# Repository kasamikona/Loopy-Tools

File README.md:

# Kasami's Loopy Tools Collection

This is a collection of tools, scripts and info that I have created/gathered in my research and
development work on the Casio Loopy. I'm working towards splitting some parts off into dedicated repos.

**Please do not use my tools for creating controversial or offensive content.**  
I feel that the demographic of the Loopy including the modern community is not a suitable place for this.
I can't stop you from doing anything, but I will blacklist you and certainly won't provide support if you do so.
You may contact me privately if you want more of an explanation of why this notice is here.

## Related Repositories

- [Loopy-Schematics](https://github.com/kasamikona/Loopy-Schematics): Schematics for various parts and accessories.
- [loopy-homebrew-template](https://github.com/kasamikona/loopy-homebrew-template): A barebones template for homebrew.

## Repo Contents

- Documentation: Research findings and datasheets.
- Hardware: Parts for custom designed hardware.
- SerialDumper: A tool to dump cartridges using the Loopy console itself with a serial mod.
- Tools: General tools and scripts for ROM analysis and manipulation etc.
- Wanwan: Tools and scripts focused on researching and modifying the Wanwan Aijou Monogatari game.

## Licensing

Documentation and informational sections are provided on a "do what you like" basis.
Code sections may contain an appropriate LICENSE.txt to refer to,
or may have no license in which case please ask me or treat it as non-free.
In general I am assuming non-commercial use and provide no warranty.
If you have any doubts about these points, please ask!

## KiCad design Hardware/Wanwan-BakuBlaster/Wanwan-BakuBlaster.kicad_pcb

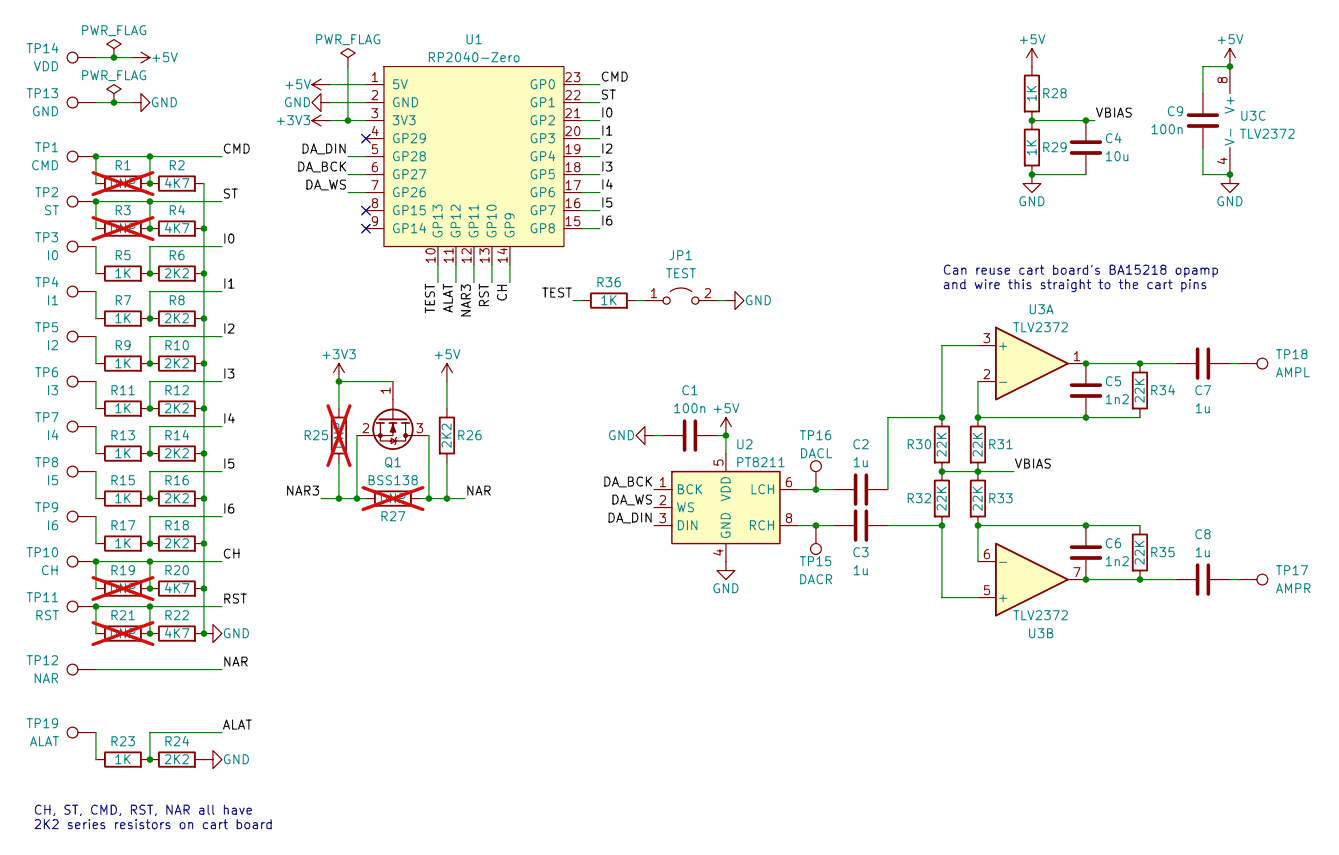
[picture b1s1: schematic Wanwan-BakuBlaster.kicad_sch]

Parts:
C1, C9: 100n; C_0805_2012Metric
C2, C3, C7, C8: 1u; C_1206_3216Metric
C4: 10u; C_1206_3216Metric
C5, C6: 1n2; C_0805_2012Metric
JP1: TEST; SolderJumper-2_P1.3mm_Open_RoundedPad1.0x1.5mm
Q1: BSS138; SOT-23
R1, R3, R19, R21, R25, R27: DNP; R_0603_1608Metric; not fitted
R2, R4, R20, R22: 4K7; R_0603_1608Metric
R5, R7, R9, R11, R13, R15, R17, R23, R28, R29, R36: 1K; R_0603_1608Metric
R6, R8, R10, R12, R14, R16, R18, R24, R26: 2K2; R_0603_1608Metric
R30, R31, R32, R33, R34, R35: 22K; R_0603_1608Metric
TP1: CMD; Hookup-Pad-Small
TP2: ST; Hookup-Pad-Small
TP3: I0; Hookup-Pad-Small
TP4: I1; Hookup-Pad-Small
TP5: I2; Hookup-Pad-Small
TP6: I3; Hookup-Pad-Small
TP7: I4; Hookup-Pad-Small
TP8: I5; Hookup-Pad-Small
TP9: I6; Hookup-Pad-Small
TP10: CH; Hookup-Pad-Small
TP11: RST; Hookup-Pad-Small
TP12: NAR; Hookup-Pad-Small
TP13: GND; Hookup-Pad-Small
TP14: VDD; Hookup-Pad-Small
TP15: DACR; Hookup-Pad-Small
TP16: DACL; Hookup-Pad-Small
TP17: AMPR; Hookup-Pad-Small
TP18: AMPL; Hookup-Pad-Small
TP19: ALAT; Hookup-Pad-Small
U1: RP2040-Zero
U2: PT8211; SO-8_3.9x4.9mm_P1.27mm
U3: TLV2372; SO-8_3.9x4.9mm_P1.27mm

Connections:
+3V3: Q1.1 (G), R25.1, U1.3 (3V3)
+5V: C1.2, C9.1, R26.1, R28.1, TP14.1, U1.1 (5V), U2.5 (VDD), U3.8 (V+)
/ALAT: R23.2, R24.1, U1.11 (GP12)
/CH: R19.1, R19.2, R20.1, TP10.1, U1.14 (GP9)
/CMD: R1.1, R1.2, R2.1, TP1.1, U1.23 (GP0)
/DA_BCK: U1.6 (GP27), U2.1 (BCK)
/DA_DIN: U1.5 (GP28), U2.3 (DIN)
/DA_WS: U1.7 (GP26), U2.2 (WS)
/I0: R5.2, R6.1, U1.21 (GP2)
/I1: R7.2, R8.1, U1.20 (GP3)
/I2: R9.2, R10.1, U1.19 (GP4)
/I3: R11.2, R12.1, U1.18 (GP5)
/I4: R13.2, R14.1, U1.17 (GP6)
/I5: R15.2, R16.1, U1.16 (GP7)
/I6: R17.2, R18.1, U1.15 (GP8)
/NAR: Q1.3 (D), R26.2, R27.2, TP12.1
/NAR3: Q1.2 (S), R25.2, R27.1, U1.12 (GP11)
/RST: R21.1, R21.2, R22.1, TP11.1, U1.13 (GP10)
/ST: R3.1, R3.2, R4.1, TP2.1, U1.22 (GP1)
/TEST: R36.1, U1.10 (GP13)
/VBIAS: C4.1, R28.2, R29.1, R30.2, R31.2, R32.1, R33.1
GND: C1.1, C4.2, C9.2, JP1.2 (B), R2.2, R4.2, R6.2, R8.2, R10.2, R12.2, R14.2, R16.2, R18.2, R20.2, R22.2, R24.2, R29.2, TP13.1, U1.2 (GND), U2.4 (GND), U3.4 (V-)
unnamed: C5.1, C7.1, R34.1, U3.1
unnamed: C6.2, C8.1, R35.2, U3.7
unnamed: C7.2, TP18.1
unnamed: C8.2, TP17.1
unnamed: JP1.1 (A), R36.2
unnamed: R5.1, TP3.1
unnamed: R7.1, TP4.1
unnamed: R9.1, TP5.1
unnamed: R11.1, TP6.1
unnamed: R13.1, TP7.1
unnamed: R15.1, TP8.1
unnamed: R17.1, TP9.1
unnamed: R23.1, TP19.1
unnamed: C2.1, TP16.1, U2.6 (LCH)
unnamed: C3.1, TP15.1, U2.8 (RCH)
unnamed: C2.2, R30.1, U3.3 (+)
unnamed: C5.2, R31.1, R34.2, U3.2 (-)
unnamed: C3.2, R32.2, U3.5 (+)
unnamed: C6.1, R33.2, R35.1, U3.6 (-)

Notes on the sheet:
Can reuse cart board's BA15218 opamp and wire this straight to the cart pins
CH, ST, CMD, RST, NAR all have 2K2 series resistors on cart board

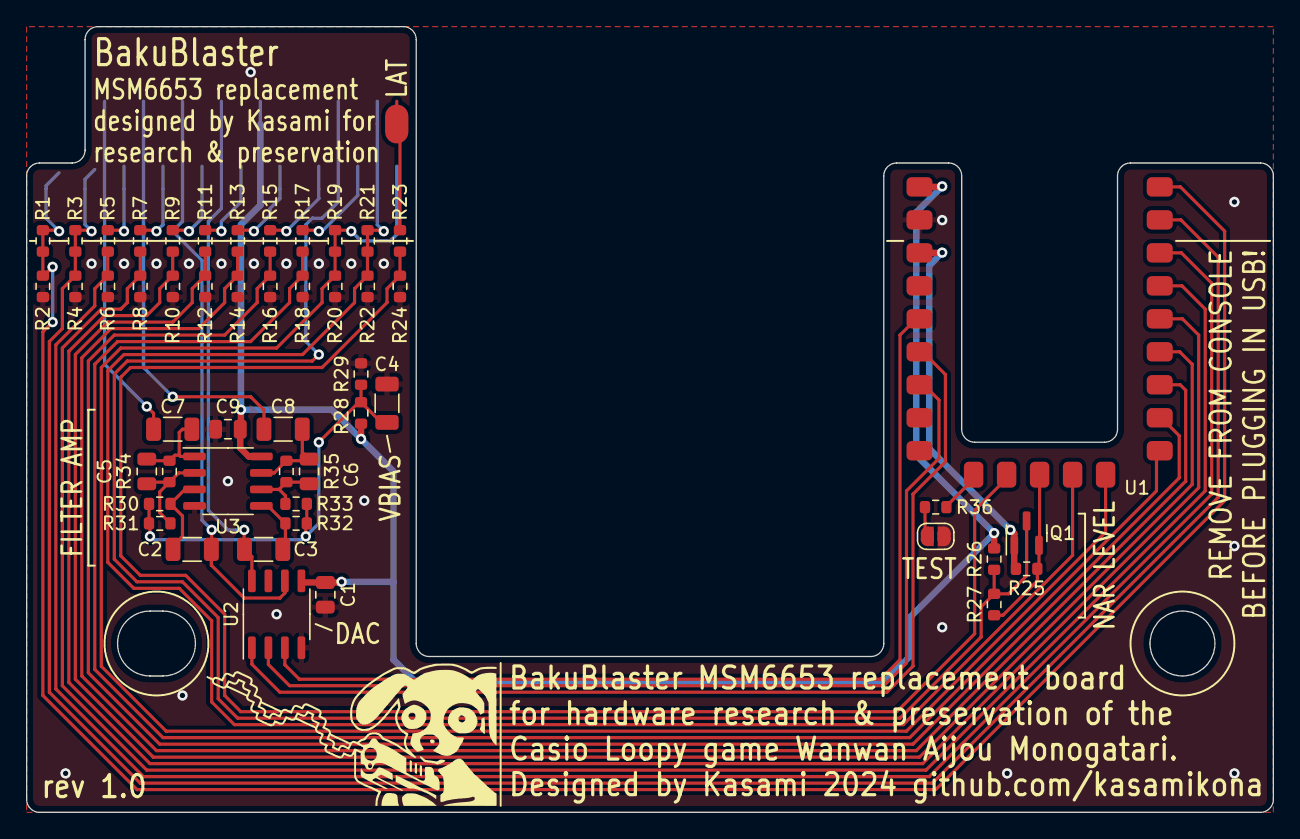
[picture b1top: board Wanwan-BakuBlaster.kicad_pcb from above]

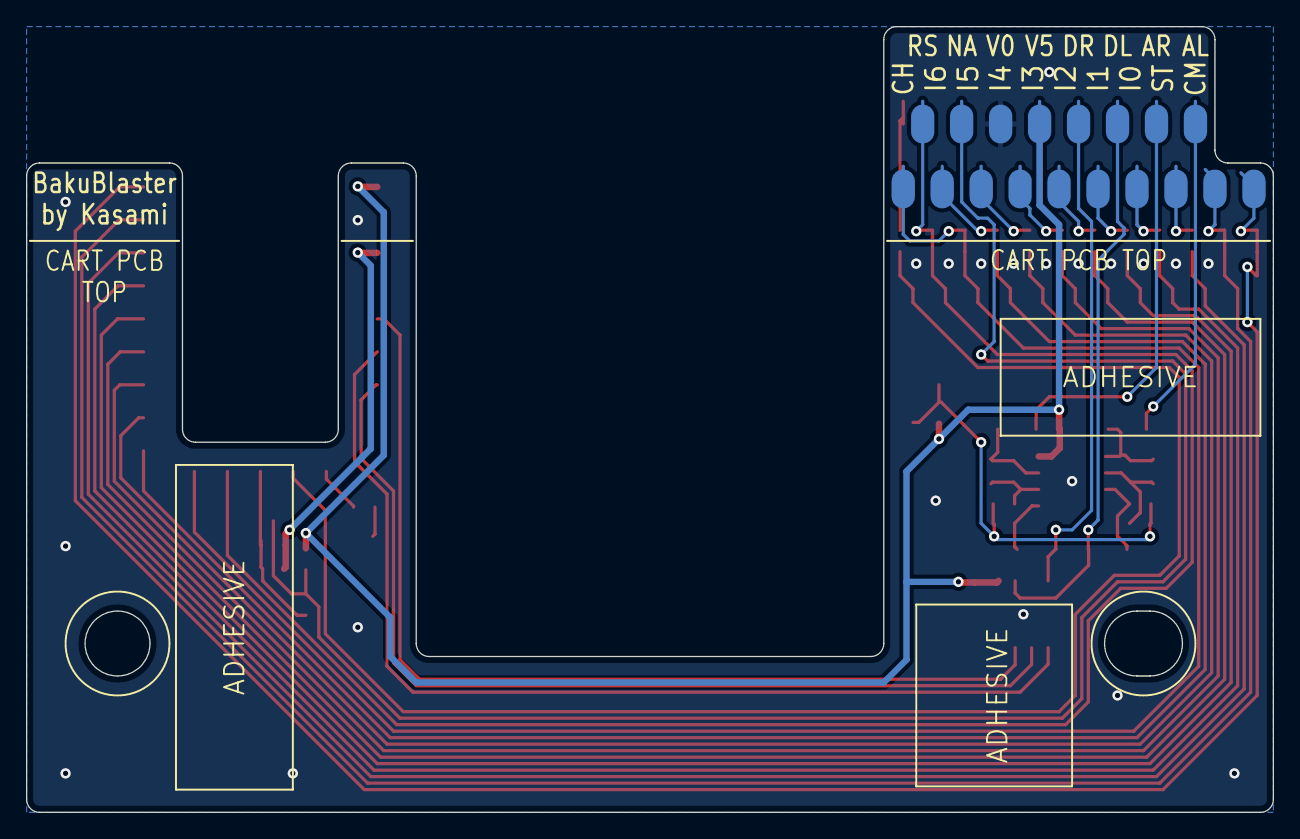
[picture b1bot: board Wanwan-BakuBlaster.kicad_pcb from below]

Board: 2 copper layers, 96.0 x 60.5 mm, 69 parts (18 on the bottom side), 41 nets.

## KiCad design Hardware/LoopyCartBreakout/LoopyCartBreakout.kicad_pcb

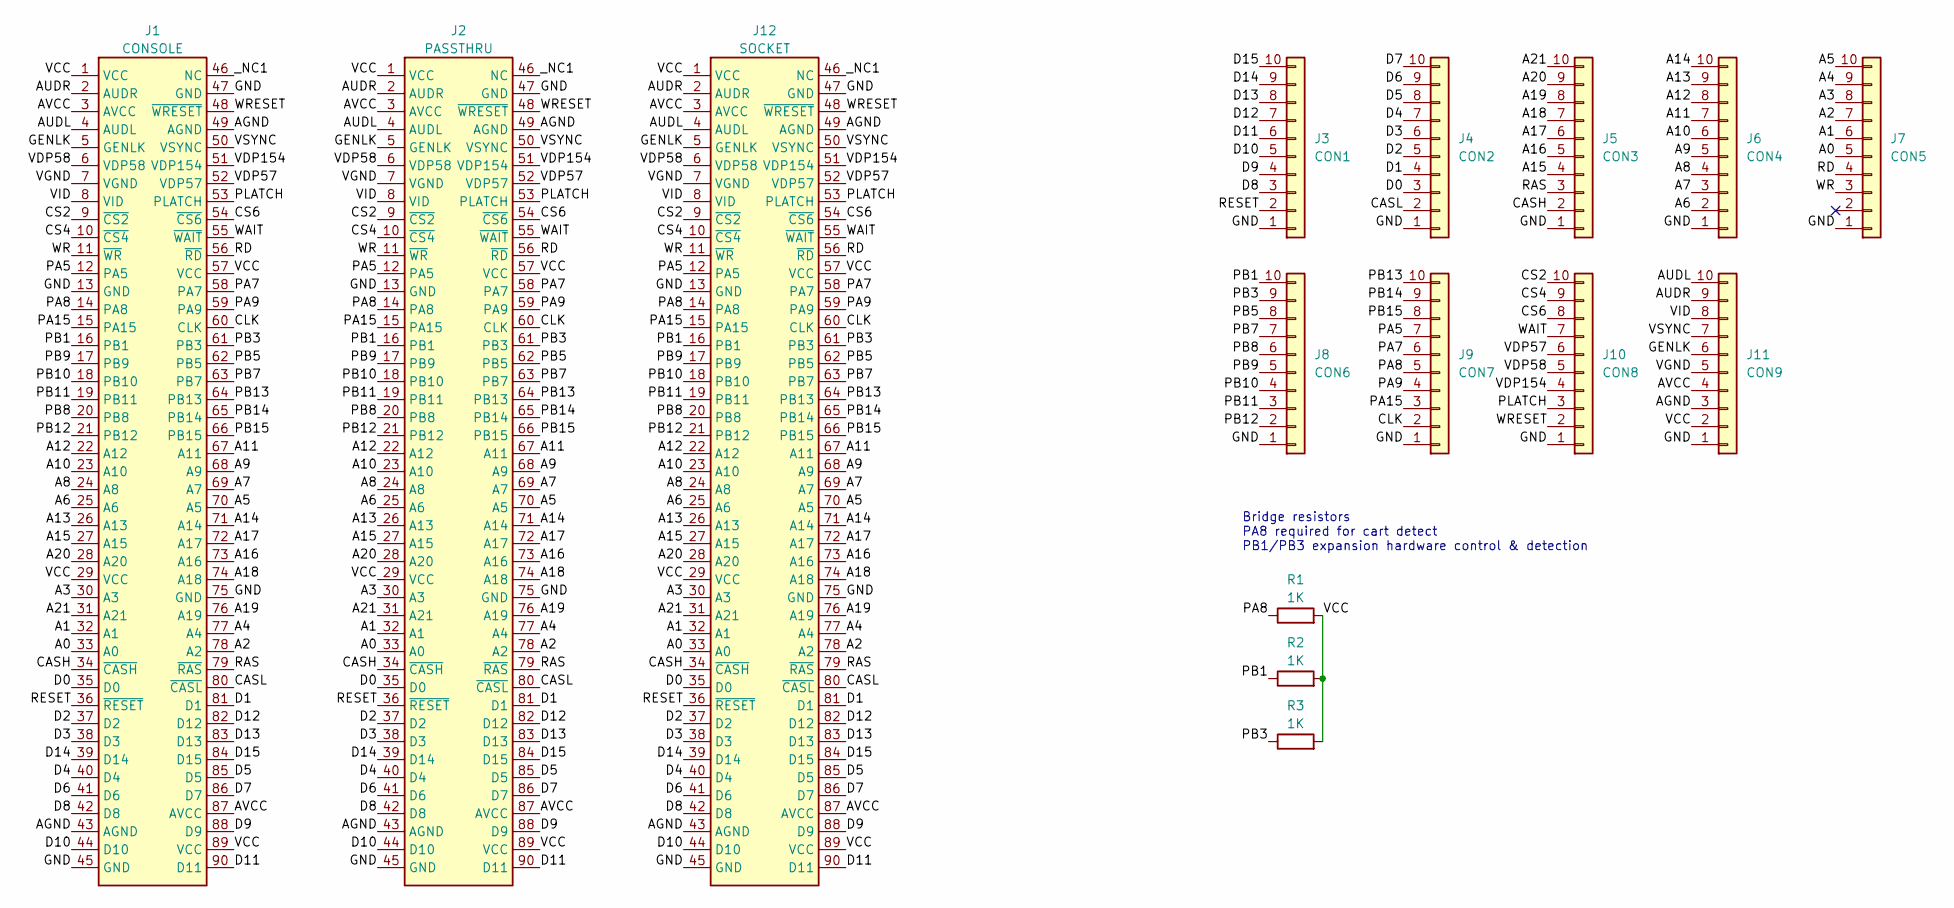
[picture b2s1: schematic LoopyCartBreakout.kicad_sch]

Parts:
J1: CONSOLE; Loopy-Cart-Edge
J2: PASSTHRU; Loopy-Cart-Passthru
J3: CON1; PinHeader_1x10_P2.54mm_Vertical
J4: CON2; PinHeader_1x10_P2.54mm_Vertical
J5: CON3; PinHeader_1x10_P2.54mm_Vertical
J6: CON4; PinHeader_1x10_P2.54mm_Vertical
J7: CON5; PinHeader_1x10_P2.54mm_Vertical
J8: CON6; PinHeader_1x10_P2.54mm_Vertical
J9: CON7; PinHeader_1x10_P2.54mm_Vertical
J10: CON8; PinHeader_1x10_P2.54mm_Vertical
J11: CON9; PinHeader_1x10_P2.54mm_Vertical
J12: SOCKET; Loopy-Cart-Socket-Short
R1, R2, R3: 1K; R_0603_1608Metric_Pad0.98x0.95mm_HandSolder

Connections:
/A0: J1.33 (A0), J2.33 (A0), J7.5, J12.33 (A0)
/A1: J1.32 (A1), J2.32 (A1), J7.6, J12.32 (A1)
/A2: J1.78 (A2), J2.78 (A2), J7.7, J12.78 (A2)
/A3: J1.30 (A3), J2.30 (A3), J7.8, J12.30 (A3)
/A4: J1.77 (A4), J2.77 (A4), J7.9, J12.77 (A4)
/A5: J1.70 (A5), J2.70 (A5), J7.10, J12.70 (A5)
/A6: J1.25 (A6), J2.25 (A6), J6.2, J12.25 (A6)
/A7: J1.69 (A7), J2.69 (A7), J6.3, J12.69 (A7)
/A8: J1.24 (A8), J2.24 (A8), J6.4, J12.24 (A8)
/A9: J1.68 (A9), J2.68 (A9), J6.5, J12.68 (A9)
/A10: J1.23 (A10), J2.23 (A10), J6.6, J12.23 (A10)
/A11: J1.67 (A11), J2.67 (A11), J6.7, J12.67 (A11)
/A12: J1.22 (A12), J2.22 (A12), J6.8, J12.22 (A12)
/A13: J1.26 (A13), J2.26 (A13), J6.9, J12.26 (A13)
/A14: J1.71 (A14), J2.71 (A14), J6.10, J12.71 (A14)
/A15: J1.27 (A15), J2.27 (A15), J5.4, J12.27 (A15)
/A16: J1.73 (A16), J2.73 (A16), J5.5, J12.73 (A16)
/A17: J1.72 (A17), J2.72 (A17), J5.6, J12.72 (A17)
/A18: J1.74 (A18), J2.74 (A18), J5.7, J12.74 (A18)
/A19: J1.76 (A19), J2.76 (A19), J5.8, J12.76 (A19)
/A20: J1.28 (A20), J2.28 (A20), J5.9, J12.28 (A20)
/A21: J1.31 (A21), J2.31 (A21), J5.10, J12.31 (A21)
/AGND: J1.43 (AGND), J1.49 (AGND), J2.43 (AGND), J2.49 (AGND), J11.3, J12.43 (AGND), J12.49 (AGND)
/AUDL: J1.4 (AUDL), J2.4 (AUDL), J11.10, J12.4 (AUDL)
/AUDR: J1.2 (AUDR), J2.2 (AUDR), J11.9, J12.2 (AUDR)
/AVCC: J1.3 (AVCC), J1.87 (AVCC), J2.3 (AVCC), J2.87 (AVCC), J11.4, J12.3 (AVCC), J12.87 (AVCC)
/CASH: J1.34 (~CASH), J2.34 (~CASH), J5.2, J12.34 (~CASH)
/CASL: J1.80 (~CASL), J2.80 (~CASL), J4.2, J12.80 (~CASL)
/CLK: J1.60 (CLK), J2.60 (CLK), J9.2, J12.60 (CLK)
/CS2: J1.9 (~CS2), J2.9 (~CS2), J10.10, J12.9 (~CS2)
/CS4: J1.10 (~CS4), J2.10 (~CS4), J10.9, J12.10 (~CS4)
/CS6: J1.54 (~CS6), J2.54 (~CS6), J10.8, J12.54 (~CS6)
/D0: J1.35 (D0), J2.35 (D0), J4.3, J12.35 (D0)
/D1: J1.81 (D1), J2.81 (D1), J4.4, J12.81 (D1)
/D2: J1.37 (D2), J2.37 (D2), J4.5, J12.37 (D2)
/D3: J1.38 (D3), J2.38 (D3), J4.6, J12.38 (D3)
/D4: J1.40 (D4), J2.40 (D4), J4.7, J12.40 (D4)
/D5: J1.85 (D5), J2.85 (D5), J4.8, J12.85 (D5)
/D6: J1.41 (D6), J2.41 (D6), J4.9, J12.41 (D6)
/D7: J1.86 (D7), J2.86 (D7), J4.10, J12.86 (D7)
/D8: J1.42 (D8), J2.42 (D8), J3.3, J12.42 (D8)
/D9: J1.88 (D9), J2.88 (D9), J3.4, J12.88 (D9)
/D10: J1.44 (D10), J2.44 (D10), J3.5, J12.44 (D10)
/D11: J1.90 (D11), J2.90 (D11), J3.6, J12.90 (D11)
/D12: J1.82 (D12), J2.82 (D12), J3.7, J12.82 (D12)
/D13: J1.83 (D13), J2.83 (D13), J3.8, J12.83 (D13)
/D14: J1.39 (D14), J2.39 (D14), J3.9, J12.39 (D14)
/D15: J1.84 (D15), J2.84 (D15), J3.10, J12.84 (D15)
/GENLK: J1.5 (GENLK), J2.5 (GENLK), J11.6, J12.5 (GENLK)
/GND: J1.13 (GND), J1.45 (GND), J1.47 (GND), J1.75 (GND), J2.13 (GND), J2.45 (GND), J2.47 (GND), J2.75 (GND), J3.1, J4.1, J5.1, J6.1, J7.1, J8.1, J9.1, J10.1, J11.1, J12.13 (GND), J12.45 (GND), J12.47 (GND), J12.75 (GND)
/PA5: J1.12 (PA5), J2.12 (PA5), J9.7, J12.12 (PA5)
/PA7: J1.58 (PA7), J2.58 (PA7), J9.6, J12.58 (PA7)
/PA8: J1.14 (PA8), J2.14 (PA8), J9.5, J12.14 (PA8), R1.1
/PA9: J1.59 (PA9), J2.59 (PA9), J9.4, J12.59 (PA9)
/PA15: J1.15 (PA15), J2.15 (PA15), J9.3, J12.15 (PA15)
/PB1: J1.16 (PB1), J2.16 (PB1), J8.10, J12.16 (PB1), R2.1
/PB3: J1.61 (PB3), J2.61 (PB3), J8.9, J12.61 (PB3), R3.1
/PB5: J1.62 (PB5), J2.62 (PB5), J8.8, J12.62 (PB5)
/PB7: J1.63 (PB7), J2.63 (PB7), J8.7, J12.63 (PB7)
/PB8: J1.20 (PB8), J2.20 (PB8), J8.6, J12.20 (PB8)
/PB9: J1.17 (PB9), J2.17 (PB9), J8.5, J12.17 (PB9)
/PB10: J1.18 (PB10), J2.18 (PB10), J8.4, J12.18 (PB10)
/PB11: J1.19 (PB11), J2.19 (PB11), J8.3, J12.19 (PB11)
/PB12: J1.21 (PB12), J2.21 (PB12), J8.2, J12.21 (PB12)
/PB13: J1.64 (PB13), J2.64 (PB13), J9.10, J12.64 (PB13)
/PB14: J1.65 (PB14), J2.65 (PB14), J9.9, J12.65 (PB14)
/PB15: J1.66 (PB15), J2.66 (PB15), J9.8, J12.66 (PB15)
/PLATCH: J1.53 (PLATCH), J2.53 (PLATCH), J10.3, J12.53 (PLATCH)
/RAS: J1.79 (~RAS), J2.79 (~RAS), J5.3, J12.79 (~RAS)
/RD: J1.56 (~RD), J2.56 (~RD), J7.4, J12.56 (~RD)
/RESET: J1.36 (~RESET), J2.36 (~RESET), J3.2, J12.36 (~RESET)
/VCC: J1.1 (VCC), J1.29 (VCC), J1.57 (VCC), J1.89 (VCC), J2.1 (VCC), J2.29 (VCC), J2.57 (VCC), J2.89 (VCC), J11.2, J12.1 (VCC), J12.29 (VCC), J12.57 (VCC), J12.89 (VCC), R1.2, R2.2, R3.2
/VDP57: J1.52 (VDP57), J2.52 (VDP57), J10.6, J12.52 (VDP57)
/VDP58: J1.6 (VDP58), J2.6 (VDP58), J10.5, J12.6 (VDP58)
/VDP154: J1.51 (VDP154), J2.51 (VDP154), J10.4, J12.51 (VDP154)
/VGND: J1.7 (VGND), J2.7 (VGND), J11.5, J12.7 (VGND)
/VID: J1.8 (VID), J2.8 (VID), J11.8, J12.8 (VID)
/VSYNC: J1.50 (VSYNC), J2.50 (VSYNC), J11.7, J12.50 (VSYNC)
/WAIT: J1.55 (~WAIT), J2.55 (~WAIT), J10.7, J12.55 (~WAIT)
/WR: J1.11 (~WR), J2.11 (~WR), J7.3, J12.11 (~WR)
/WRESET: J1.48 (~WRESET), J2.48 (~WRESET), J10.2, J12.48 (~WRESET)
/_NC1: J1.46 (NC), J2.46 (NC), J12.46 (NC)

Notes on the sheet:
Bridge resistors PA8 required for cart detect PB1/PB3 expansion hardware control & detection

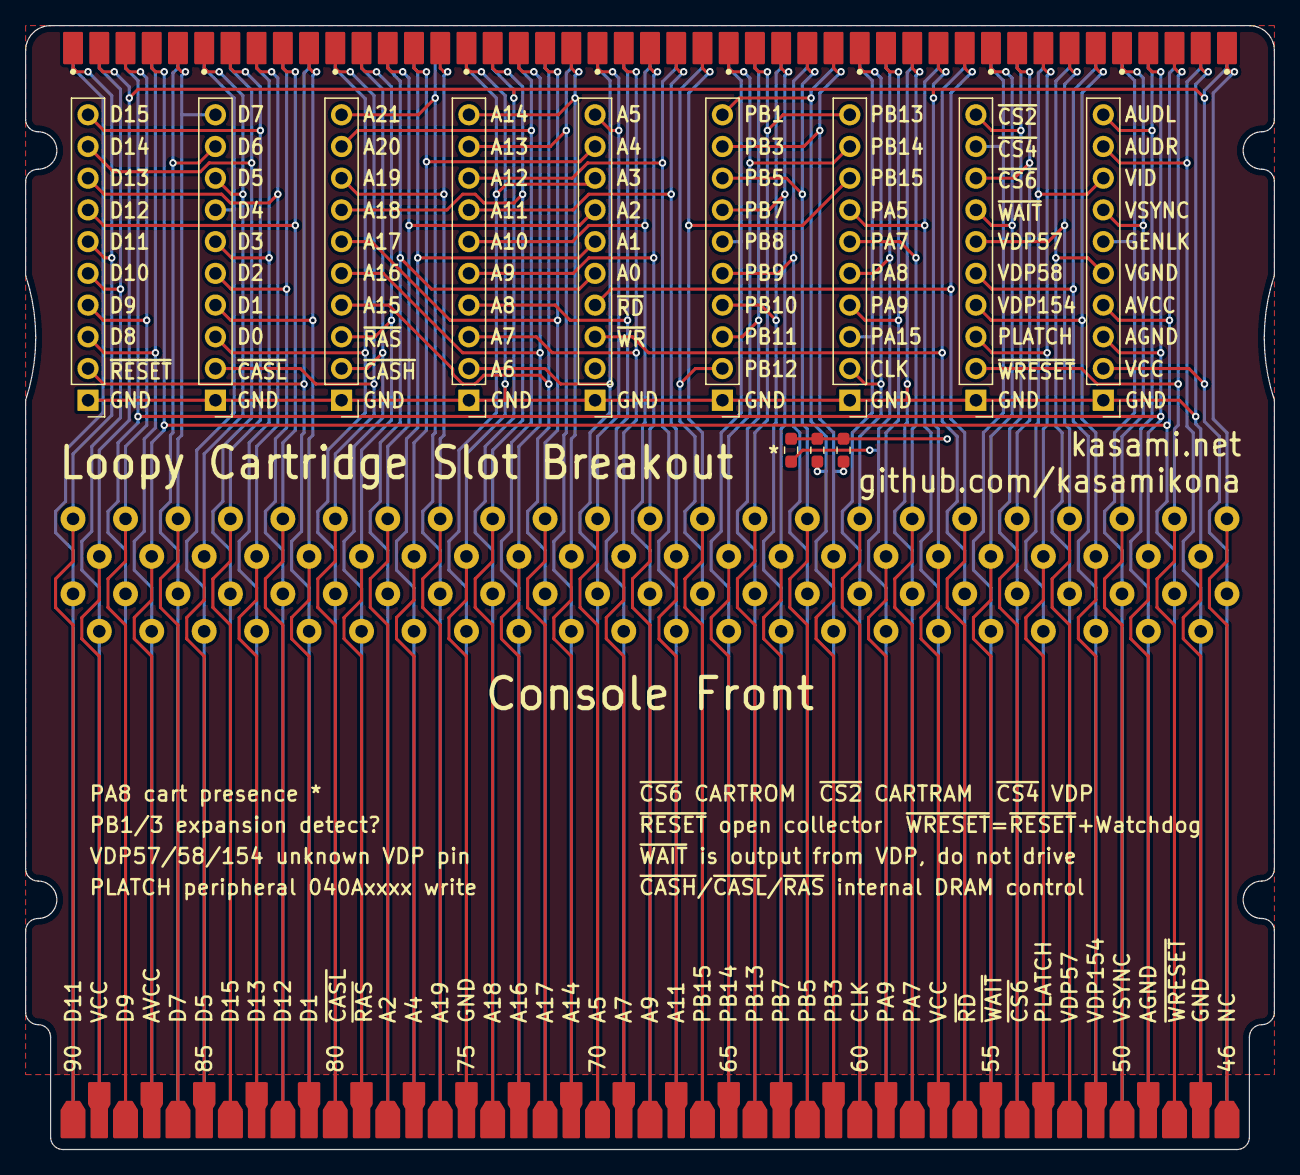
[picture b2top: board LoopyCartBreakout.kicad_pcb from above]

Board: 2 copper layers, 100.0 x 90.0 mm, 15 parts (1 on the bottom side), 82 nets.

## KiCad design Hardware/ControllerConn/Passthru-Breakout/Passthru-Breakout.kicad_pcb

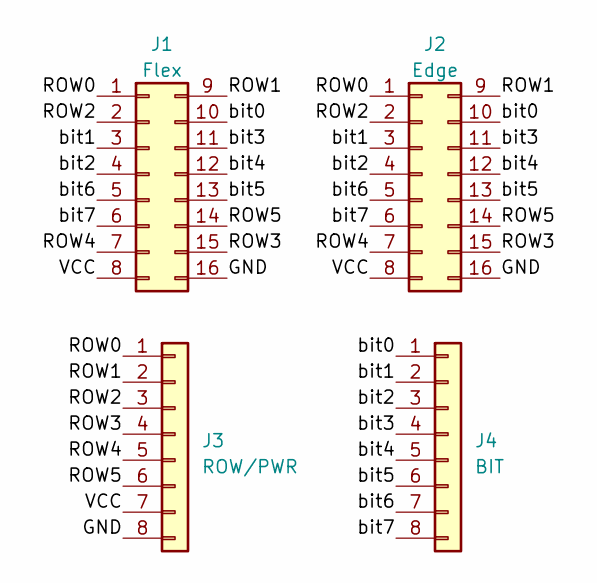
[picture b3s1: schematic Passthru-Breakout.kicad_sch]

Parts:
J1: Flex; Flex-Bonding
J2: Edge; Edge-Conn
J3: ROW/PWR; PinHeader_1x08_P2.54mm_Vertical
J4: BIT; PinHeader_1x08_P2.54mm_Vertical

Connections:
/GND: J1.16, J2.16, J3.8
/ROW0: J1.1, J2.1, J3.1
/ROW1: J1.9, J2.9, J3.2
/ROW2: J1.2, J2.2, J3.3
/ROW3: J1.15, J2.15, J3.4
/ROW4: J1.7, J2.7, J3.5
/ROW5: J1.14, J2.14, J3.6
/VCC: J1.8, J2.8, J3.7
/bit0: J1.10, J2.10, J4.1
/bit1: J1.3, J2.3, J4.2
/bit2: J1.4, J2.4, J4.3
/bit3: J1.11, J2.11, J4.4
/bit4: J1.12, J2.12, J4.5
/bit5: J1.13, J2.13, J4.6
/bit6: J1.5, J2.5, J4.7
/bit7: J1.6, J2.6, J4.8

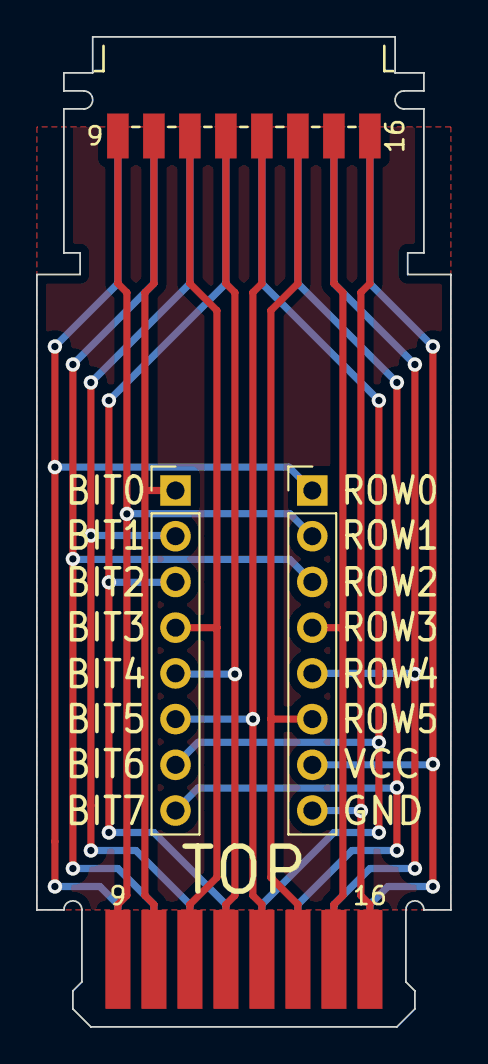
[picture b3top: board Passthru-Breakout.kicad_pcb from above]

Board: 2 copper layers, 23.0 x 55.0 mm, 4 parts (0 on the bottom side), 16 nets.

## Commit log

2023-06-24 Prepare for publish
2023-06-25 Add ROM structure documentation
2023-06-25 Add more dumper info and unswapped binary
2023-07-16 Add compiler template files ;)
2023-07-18 Fix whitespace, use include dir properly
2023-08-08 Add cartridge breakout boards for future FPGA testing and proper card-edge production
2023-08-21 Add Wanwan font dumper
2023-08-22 Reorganize compiler template and normalize line endings
2023-08-22 Add zlib license to compiler template project
2023-08-22 Rename shregs.h to something more sensible
2023-08-22 Add source for serial dumper ROM
2023-08-22 Reorganize repo a bit and add a primary readme as an index
2023-08-22 Update compiler setup to use Wonderful Toolchain
2023-08-26 Add incomplete component listing for power/av board with caps list
2023-08-26 Add description of music track format
2023-08-27 Fix BiosPlayBGM signature in description
2023-08-28 List rest of power AV board components as currently identifiable
2023-08-28 Reserve low memory for BIOS state and use Renesas ABI
2023-08-28 Fix part number
2023-08-28 Add warning about C504 reverse polarity
2023-08-29 Fix breakout to separate VGND
2023-08-30 Update makefile for new toolchain
2023-09-01 Update power AV capacitor info, add regulator IC compatible part
2023-09-14 Update ROM structure info
2023-09-14 Fix table formatting stupidity
2023-10-20 Fix music format and add power board note about VCC adjustment
2023-10-20 Add tools for generating and converting bitmap images
2023-10-20 Controller connector dimensional drawing (reverse engineered)
2023-12-17 CompilerTemplate: partially rewrite loopy.ld
    - moved C-runtime initialization to crt0.c
    - C-runtime initialization now includes C++ static initializers
    - added C++ Makefile rule
    - rom building is split to "elf" and "bin" parts; this makes it easier
    to view the outcome of running the linker script
    - copy-pasted DWARF debugging sections from the default gcc linker
2023-12-18 loopy.ld: adjust "last address" calculation
    This uses the size of the data in rom as the "last address" in the
    cartridge header.
    - move gitignore directives to CompilerTemplate
    - Makefile: remove LoopyMSE hack
    - Makefile: use the ROM variable more consistently
    - Makefile: move path separator inside the TOOLBIN variable
2024-01-13 Add various schematics and WIP controller connector project
2024-01-13 Fix SVG background
2024-01-14 Mouse capacitors measured
2024-01-19 Wanwan font: separate planes and reinjection tool
2024-01-19 Let's not have a folder full of PNGs actually
2024-01-19 Add other wanwan stuff that totally should've been here the whole time
2024-01-19 Fix geometry errors in connector shell, remove extra files
2024-01-23 Fix audio resistor references, recommend bridging to fix level
2024-01-23 Don't recommend risking fried opamps actually
2024-01-23 Optimize string regioning with bitfield
2024-01-23 Update wanwan strings script, remove bad string from clean list
2024-02-04 Move schematics to separate repo
2024-02-08 Please don't do that.
2024-03-02 crt0.c: data_load_start typo
    Previously this was making the C symbol `__data_load_start` equal to
    the linker symbol `__data_link_start`, which was not intended.
2024-03-02 Update music format info
2024-03-02 Remove byte-swapped target from makefile
2024-03-02 Update readme to reflect current state of the project
2024-03-08 Do padding in fixsum instead of fighting with ld
2024-03-08 Rename fixsum to fixrom
2024-03-08 Move header to a separate source file
2024-03-08 Clarify compiler readme statement with respect to licensing
2024-03-09 Padding didn't work, fought with ld after all, now it does
2024-03-11 Correct error in channel mode numbers
2024-03-11 loopy.ld: add LMA alignment statements
    This exclusively affects output sections that use the `AT>`
    keyword.
    ld appears to have curious behavior where the alignment requirements
    of a section only respected as a coincidence of the case where
    LMA==VMA. If an alternate LMA is specified with AT> , alignment
    requirements are completely ignored when the LMA is created.
2024-06-15 Update cart breakout board & treat kicad files as binary
2024-06-15 Publish BakuBlaster replacement wanwan PCM hardware, no firmware yet
2024-06-23 Rename project files
2024-06-23 Update clearances
2024-10-08 Number MIDI channels from 1-4 and other tidyup of music format
2024-10-08 Update Wanwan text stuff that I did nine months ago
2024-10-08 Update hardware stuff
2024-10-08 Add wanwan sprite extractor
2024-11-16 New control code handler, improve detection & repacking algorithms, remove reclean command
2024-11-16 Trust pointer list from csv instead of regathering to inject
2024-11-16 Don't explicitly quote strings, csv module handles it
2024-11-16 Fix typos in inject code
2024-11-19 Update sprite extractor to separate out decompressor
2024-11-19 Rename wanwansprite.py to wanwan_resources.py
2024-11-21 Implement compressor, add tilesheet extractor
2024-11-21 Rename wanwan_data module to wanwan_lzss
2024-11-21 Remove old test data
2024-11-21 Cleanup and add comments
2024-11-26 Add controller documentation
2024-11-26 Add more controller info
2024-12-01 Use argparse for commands
2024-12-02 Separate decoders from extractor for modularization
2024-12-02 Fix crash on truncated decompression
2024-12-02 Move files for modularization
2024-12-02 Modularize resource tool
2024-12-06 Handle resources that are 1 byte too long
2024-12-06 Add palette preview command
2024-12-06 Rework palette functions
2024-12-07 Create output dirs, rename view-palette to decode-palette
2024-12-08 Add subpalette argument to tile decoder
2024-12-08 Add metasprite decoder
2024-12-19 Clarify intentions of header notice
2025-01-25 Fix some stupid bugs in inject script
2025-01-26 Font tool: use resource table lookup
2025-01-26 Font tool: use wildcard output instead of fixed format
2025-01-26 Update resource structure info
2025-01-26 Rename file
2025-01-26 Allow injecting single planes, rework command syntax
2025-01-26 Clean up variable names
2025-01-26 Move font tool
2025-01-29 Add custom chars in string tool
2025-02-05 Update string tool for current translation state
2025-02-06 Remove remapcc argument
2025-02-06 Add patching tool for CSV patch set
2025-02-06 Patchrom exit(1) on fail
2025-02-06 Allow multiple strings with same origin
2025-02-06 Strings tool exit(1) on fail, report required space more accurately
2025-02-07 Deduplication on inject and variable alignment
2025-02-07 Split resource extraction to use section file; Add tilemap decode
2025-02-07 Resource tool exit(1) on fail
2025-02-24 Add tilesheet decode-to and encode-from grayscale
2025-02-24 Add resource inject command
2025-02-24 Add section inject command
2025-02-24 Fix error in extract-resource and print newline at start
2025-03-03 Add derive-palette and encode-image
2025-03-03 Allow working with indexed-color bitmap images
2025-03-15 Add indexed-color modes for tilesheet, share load code with bitmaps
2025-03-20 Fix missing import for grayscale image load
2025-03-30 Add file-update mode to ROM integrity tool
2025-05-23 Much needed update to compiler template
2025-05-23 Update compiler template readme
2025-05-23 Move compiler template to dedicated repo (outbound)
2025-05-23 I'm bad at markdown
2026-04-12 Publish old serial monitor rom & updated client
2026-04-14 Massive serial monitor refactor
2026-04-17 Improve state save/load feedback, connection stability
2026-04-17 Add readme for serial monitor
2026-04-17 Fix wrong return types
2026-04-17 Never skip setting baud rate
2026-04-17 Actually use block names in savestate feedback
2026-04-17 Update help string for help
2026-04-18 Update interrupt-related register names
2026-04-19 Rename dump/burst to fread/fwrite, clean up docs
2026-04-20 Simplify port open check
2026-04-22 Move reset code into protocol
2026-04-27 Add connection check in protocol
2026-04-27 Check connection on start
2026-04-27 Add register fuzzing framework and command
2026-04-27 Tidy up fuzzer scripts
